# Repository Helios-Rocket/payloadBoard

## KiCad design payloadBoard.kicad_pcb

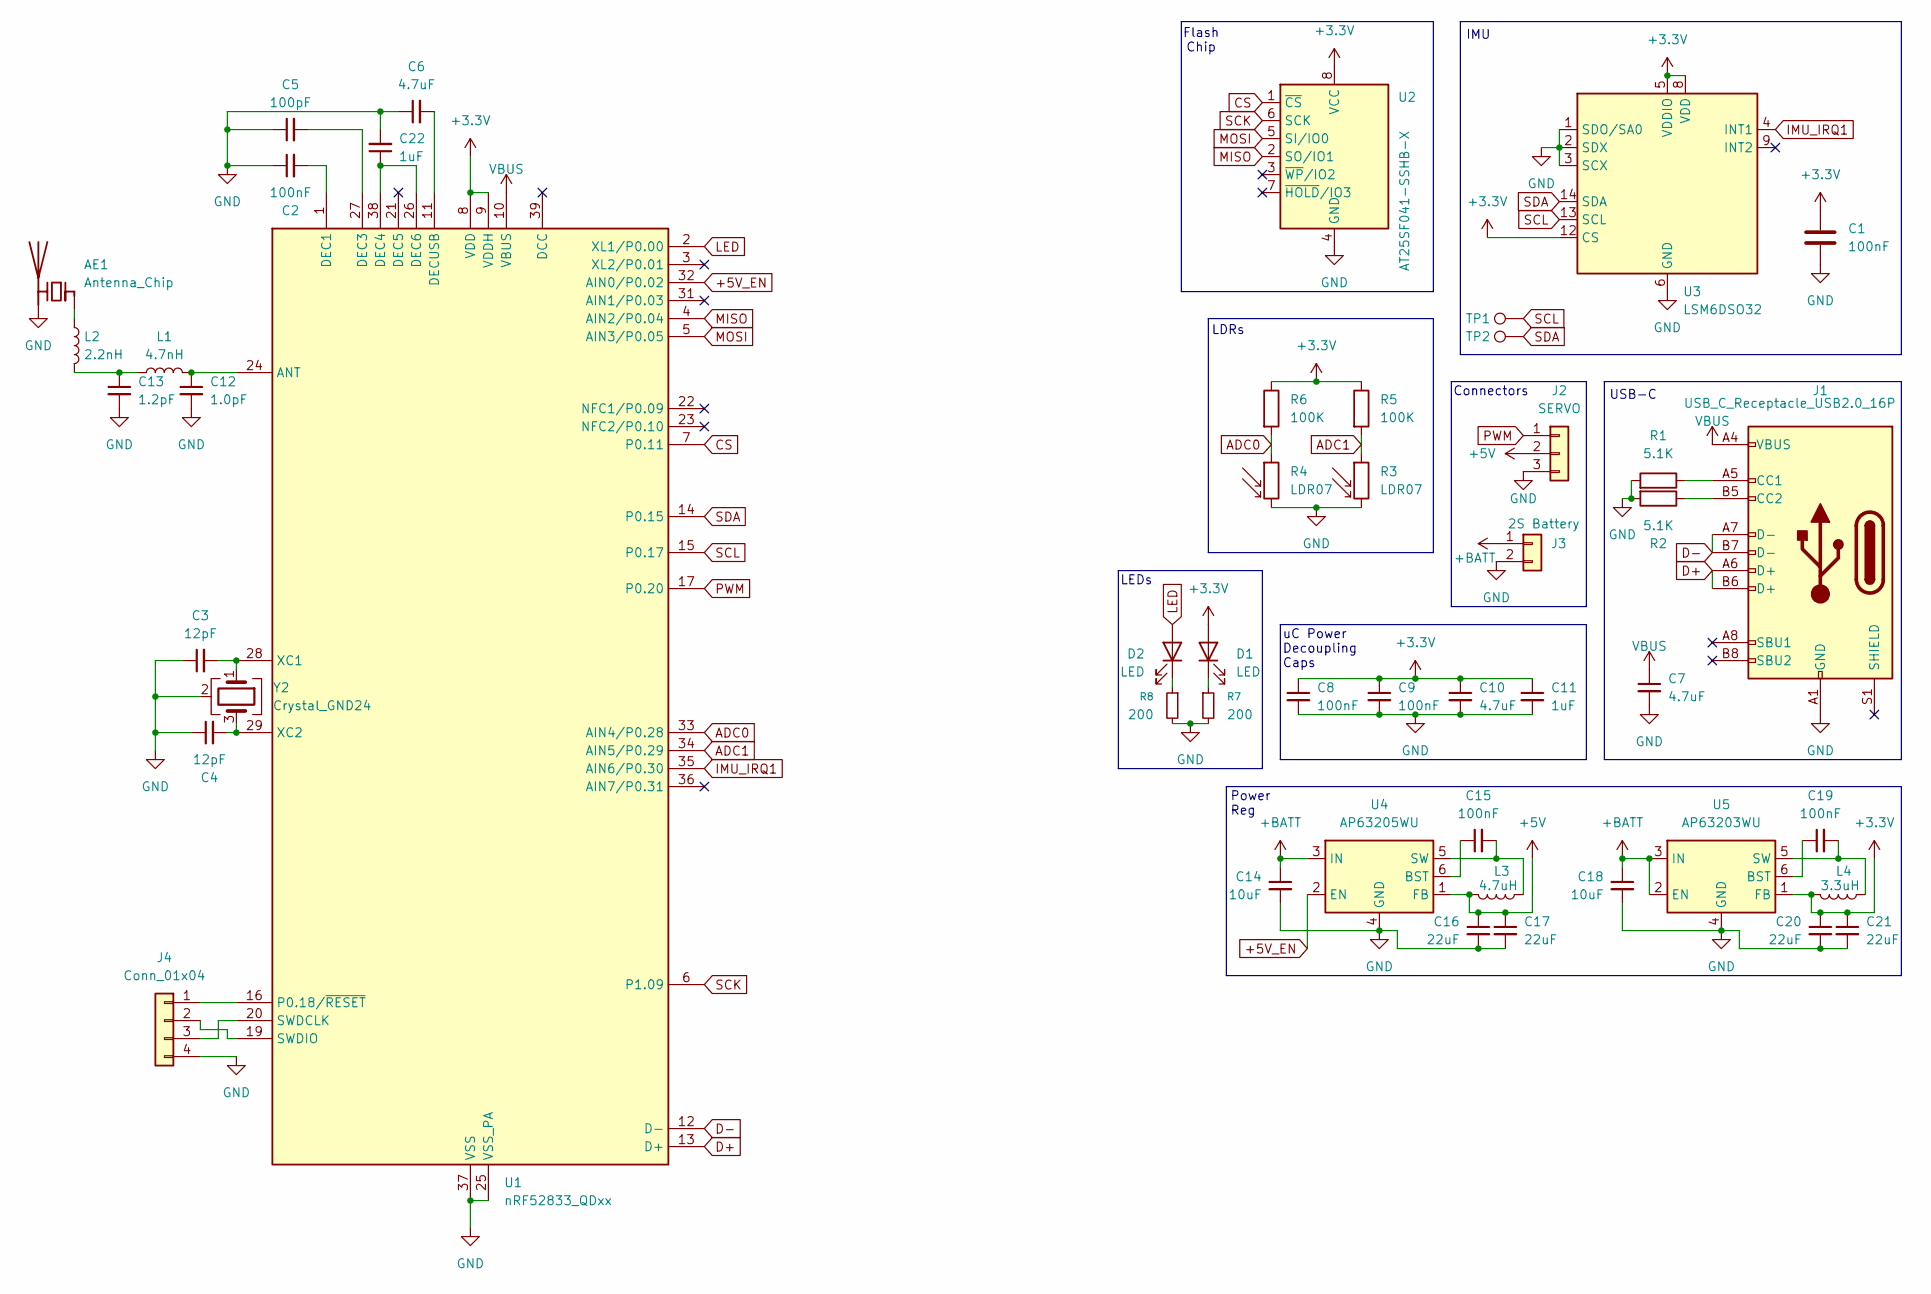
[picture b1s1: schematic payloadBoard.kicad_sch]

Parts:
AE1: Antenna_Chip; Texas_SWRA117D_2.4GHz_Left
C1, C2, C8, C9, C15, C19: 100nF; C_0402_1005Metric
C3, C4: 12pF; C_0402_1005Metric
C5: 100pF; C_0402_1005Metric
C6, C7, C10: 4.7uF; C_0402_1005Metric
C11, C22: 1uF; C_0402_1005Metric
C12: 1.0pF; C_0402_1005Metric
C13: 1.2pF; C_0402_1005Metric
C14, C18: 10uF; C_0603_1608Metric
C16, C17, C20, C21: 22uF; C_0603_1608Metric
D1, D2: LED; LED_0603_1608Metric
J1: USB_C_Receptacle_USB2.0_16P; USB_C_Receptacle_GCT_USB4105-xx-A_16P_TopMnt_Horizontal
J2: SERVO; PinHeader_1x03_P2.54mm_Vertical
J3: 2S Battery; PinHeader_1x02_P2.54mm_Vertical
J4: Conn_01x04; PinSocket_1x04_P1.00mm_Vertical
L1: 4.7nH; C_0402_1005Metric
L2: 2.2nH; C_0402_1005Metric
L3: 4.7uH; L_1008_2520Metric
L4: 3.3uH; L_1008_2520Metric
R1, R2: 5.1K; R_0402_1005Metric
R3, R4: LDR07; R_LDR_5.1x4.3mm_P3.4mm_Vertical
R5, R6: 100K; R_0402_1005Metric
R7, R8: 200; R_0402_1005Metric
TP1, TP2: TestPoint; 0.75x0.75_TestPad
U1: nRF52833_QDxx; QFN-40-1EP_5x5mm_P0.4mm_EP3.6x3.6mm
U2: AT25SF041-SSHB-X; SOIC-8_3.9x4.9mm_P1.27mm
U3: LSM6DSO32; LGA-14_3x2.5mm_P0.5mm_LayoutBorder3x4y
U4: AP63205WU; TSOT-23-6
U5: AP63203WU; TSOT-23-6
Y2: Crystal_GND24; Crystal_SMD_3225-4Pin_3.2x2.5mm

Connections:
+3.3V: C1.1, C8.1, C9.1, C10.1, C11.1, C20.1, C21.1, D1.2 (A), L4.2, R5.1, R6.1, U1.8 (VDD), U1.9 (VDDH), U1.18 (VDD), U1.30 (VDD), U1.40 (VDD), U2.8 (VCC), U3.5 (VDDIO), U3.8 (VDD), U3.12 (CS), U5.1 (FB)
+5V: C16.1, C17.1, J2.2, L3.2, U4.1 (FB)
+5V_EN: U1.32 (AIN0/P0.02), U4.2 (EN)
+BATT: C14.1, C18.1, J3.1, U4.3 (IN), U5.2 (EN), U5.3 (IN)
ADC0: R4.1, R6.2, U1.33 (AIN4/P0.28)
ADC1: R3.1, R5.2, U1.34 (AIN5/P0.29)
CS: U1.7 (P0.11), U2.1 (~CS)
D+: J1.A6 (D+), J1.B6 (D+), U1.13 (D+)
D-: J1.A7 (D-), J1.B7 (D-), U1.12 (D-)
GND: AE1.2 (PCB_Trace), C1.2, C2.1, C3.1, C4.1, C5.1, C6.1, C7.2, C8.2, C9.2, C10.2, C11.2, C12.2, C13.2, C14.2, C16.2, C17.2, C18.2, C20.2, C21.2, C22.2, J1.A1 (GND), J1.A12 (GND), J1.B1 (GND), J1.B12 (GND), J2.3, J3.2, J4.4, R1.2, R2.2, R3.2, R4.2, R7.2, R8.2, U1.25 (VSS_PA), U1.37 (VSS), U1.41 (VSS), U2.4 (GND), U3.1 (SDO/SA0), U3.2 (SDX), U3.3 (SCX), U3.6 (GND), U3.7 (GND), U4.4 (GND), U5.4 (GND), Y2.2 (G), Y2.4 (G)
IMU_IRQ1: U1.35 (AIN6/P0.30), U3.4 (INT1)
LED: D2.2 (A), U1.2 (XL1/P0.00)
MISO: U1.4 (AIN2/P0.04), U2.2 (SO/IO1)
MOSI: U1.5 (AIN3/P0.05), U2.5 (SI/IO0)
unnamed: AE1.1 (FEED), L2.1
unnamed: C13.1, L1.1, L2.2
unnamed: D1.1 (K), R7.1
unnamed: D2.1 (K), R8.1
unnamed: J1.A5 (CC1), R1.1
unnamed: J1.B5 (CC2), R2.1
unnamed: J4.1, U1.16 (P0.18/~RESET)
unnamed: J4.2, U1.19 (SWDIO)
unnamed: J4.3, U1.20 (SWDCLK)
unnamed: C12.1, L1.2, U1.24 (ANT)
unnamed: C2.2, U1.1 (DEC1)
unnamed: C5.2, U1.27 (DEC3)
unnamed: C22.1, U1.26 (DEC6), U1.38 (DEC4)
unnamed: C6.2, U1.11 (DECUSB)
unnamed: C3.2, U1.28 (XC1), Y2.1
unnamed: C4.2, U1.29 (XC2), Y2.3
unnamed: C15.1, U4.6 (BST)
unnamed: C15.2, L3.1, U4.5 (SW)
unnamed: C19.1, U5.6 (BST)
unnamed: C19.2, L4.1, U5.5 (SW)
PWM: J2.1, U1.17 (P0.20)
SCK: U1.6 (P1.09), U2.6 (SCK)
SCL: TP1.1, U1.15 (P0.17), U3.13 (SCL)
SDA: TP2.1, U1.14 (P0.15), U3.14 (SDA)
VBUS: C7.1, J1.A4 (VBUS), J1.A9 (VBUS), J1.B4 (VBUS), J1.B9 (VBUS), U1.10 (VBUS)

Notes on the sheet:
Power Reg
LEDs
USB-C
Flash Chip
LDRs
uC Power Decoupling Caps
Connectors
IMU

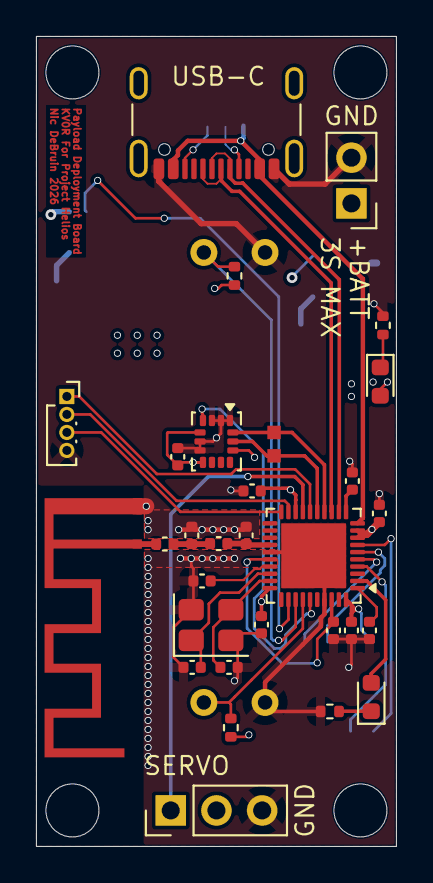
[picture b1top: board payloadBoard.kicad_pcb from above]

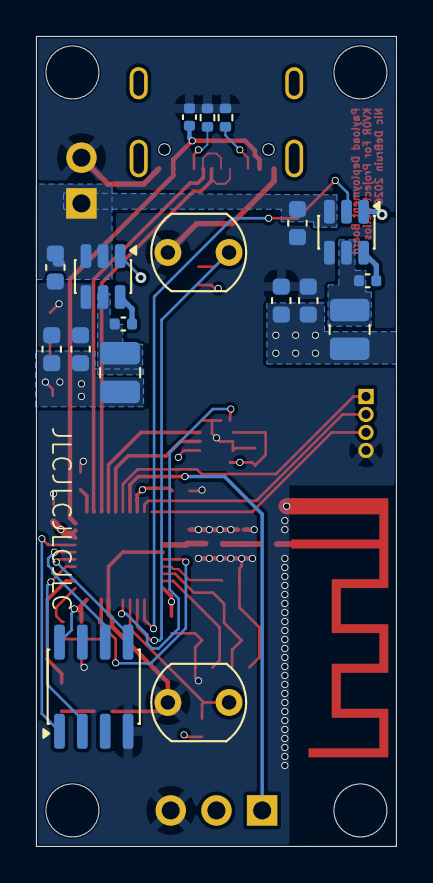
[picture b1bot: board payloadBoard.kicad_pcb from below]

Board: 4 copper layers, 20.0 x 45.0 mm, 49 parts (18 on the bottom side), 39 nets.

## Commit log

2026-02-16 most schematic minus power
2026-02-19 all footprints in but antenna, review w. sophia done
2026-02-27 version 1 finished
2026-02-27 done other than funny silkscreen
2026-02-27 fixed impedance length to proper stackup
2026-02-27 kicad git is stupid
2026-03-07 board done, plenty small
